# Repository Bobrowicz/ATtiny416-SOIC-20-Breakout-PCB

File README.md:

# ATtiny416-SOIC-20-Breakout_PCB
 SMT to DIP breakout PCB.

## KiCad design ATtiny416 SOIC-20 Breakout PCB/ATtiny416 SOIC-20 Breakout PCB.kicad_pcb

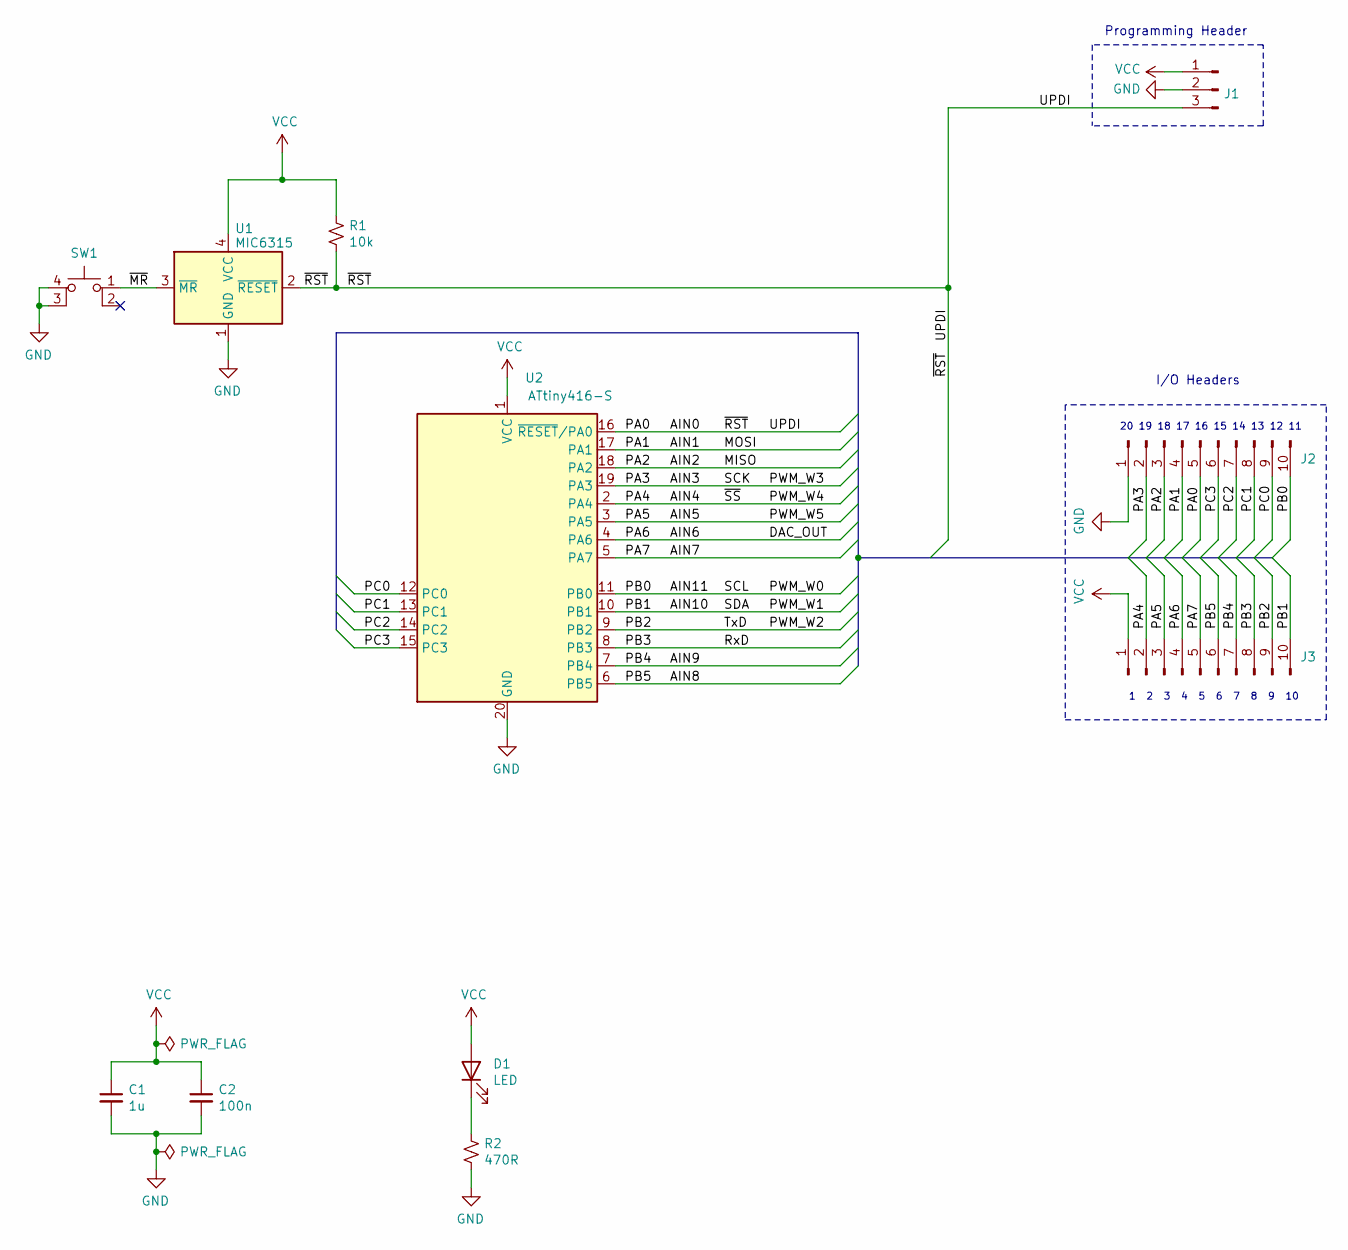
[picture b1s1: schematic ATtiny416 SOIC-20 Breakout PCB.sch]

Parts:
C1: 1u; C_0805_HandSoldering
C2: 100n; C_0805_HandSoldering
D1: LED; LED_0805_HandSoldering
J1: Conn_01x03_Male; Pin_Header_Straight_1x03_Pitch2.54mm
J2, J3: Conn_01x10_Male; Pin_Header_Straight_1x10_Pitch2.54mm
R1: 10k; R_0805_HandSoldering
R2: 470R; R_0805_HandSoldering
SW1: SW_MEC_5E; TL3305AF160QG
U1: MIC6315; SOT-143
U2: ATtiny416-S; SOIC-20W_7.5x12.8mm_Pitch1.27mm

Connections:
/AIN0: J1.3, J2.5, R1.2, U1.2 (~RESET), U2.16 (~RESET~/PA0)
/AIN1: J2.4, U2.17 (PA1)
/AIN2: J2.3, U2.18 (PA2)
/AIN3: J2.2, U2.19 (PA3)
/AIN4: J3.2, U2.2 (PA4)
/AIN5: J3.3, U2.3 (PA5)
/AIN6: J3.4, U2.4 (PA6)
/AIN7: J3.5, U2.5 (PA7)
/AIN8: J3.6, U2.6 (PB5)
/AIN9: J3.7, U2.7 (PB4)
/AIN10: J3.10, U2.10 (PB1)
/AIN11: J2.10, U2.11 (PB0)
/PB2: J3.9, U2.9 (PB2)
/PB3: J3.8, U2.8 (PB3)
/PC0: J2.9, U2.12 (PC0)
/PC1: J2.8, U2.13 (PC1)
/PC2: J2.7, U2.14 (PC2)
/PC3: J2.6, U2.15 (PC3)
/~MR: SW1.1, U1.3 (~MR)
GND: C1.2, C2.2, J1.2, J2.1, R2.2, SW1.3 (K), SW1.4 (A), U1.1 (GND), U2.20 (GND)
unnamed: D1.1 (K), R2.1
VCC: C1.1, C2.1, D1.2 (A), J1.1, J3.1, R1.1, U1.4 (VCC), U2.1 (VCC)

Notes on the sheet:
1 2 3 4 5 6 7 8 9 10
I/O Headers
Programming Header
20 19 18 17 16 15 14 13 12 11

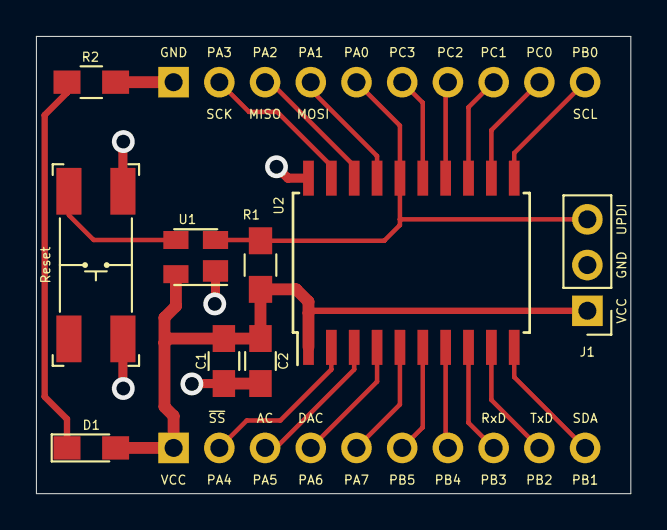
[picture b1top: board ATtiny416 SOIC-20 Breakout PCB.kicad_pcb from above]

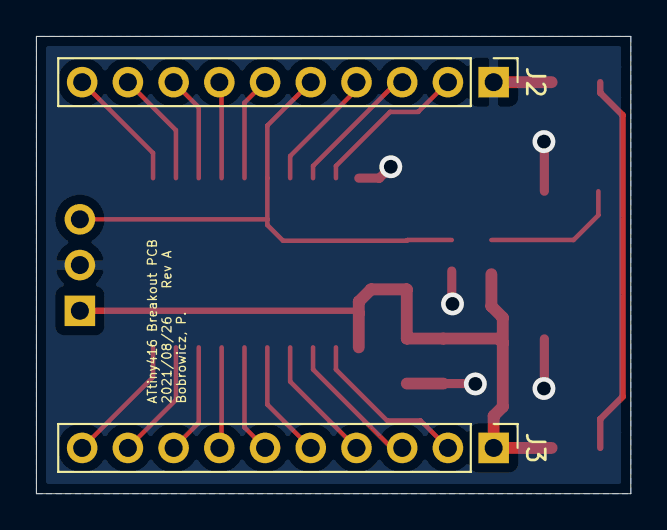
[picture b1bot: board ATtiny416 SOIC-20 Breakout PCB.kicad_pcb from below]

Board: 2 copper layers, 33.0 x 25.4 mm, 11 parts (2 on the bottom side), 22 nets.
